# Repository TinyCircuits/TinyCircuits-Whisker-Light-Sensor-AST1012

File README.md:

# TinyCircuits Wireling Light Sensor
# AST1012 Rev2

The design files are located under design_files/ for the TinyCircuits AST1012 Rev 2 PCB. This is a Wireling board which features the AMS TSL2572 ambient light sensor with built in UV rejection filter and is also capable of operating in IR light environments. Its high sensitivity range enables it to operate even behind dark glass (such as in portable applications like Smartphones).

Format is in Cadsoft Eagle format - Eagle version 6.2 was used for the original design.

For more infomation on this, check out the product page at TinyCircuits.com

# License:

Design by TinyCircuits.
All design files are released under the Creative Commons Attribution Share-Alike 3.0 License, see the following link for details: http://creativecommons.org/licenses/by-sa/3.0

All text above must be included in any redistribution or derived design

This project uses designs and concepts developed as part of the Arduino project and the LilyPad project.  The TinyCircuits design files themselves (schematics, PCB and libraries) are not directly derived from these works' design files and have been created new, however the concepts and basic architecture behind the TinyDuino and TinyLily products are derived and we thank the hard work of the organizations below for their contributions to open-source hardware:
  
Original Arduino Uno Design by Team Arduino

LilyPad Arduino Design by Leah Buechley and Sparkfun Electronics

Please support the open-source hardware community

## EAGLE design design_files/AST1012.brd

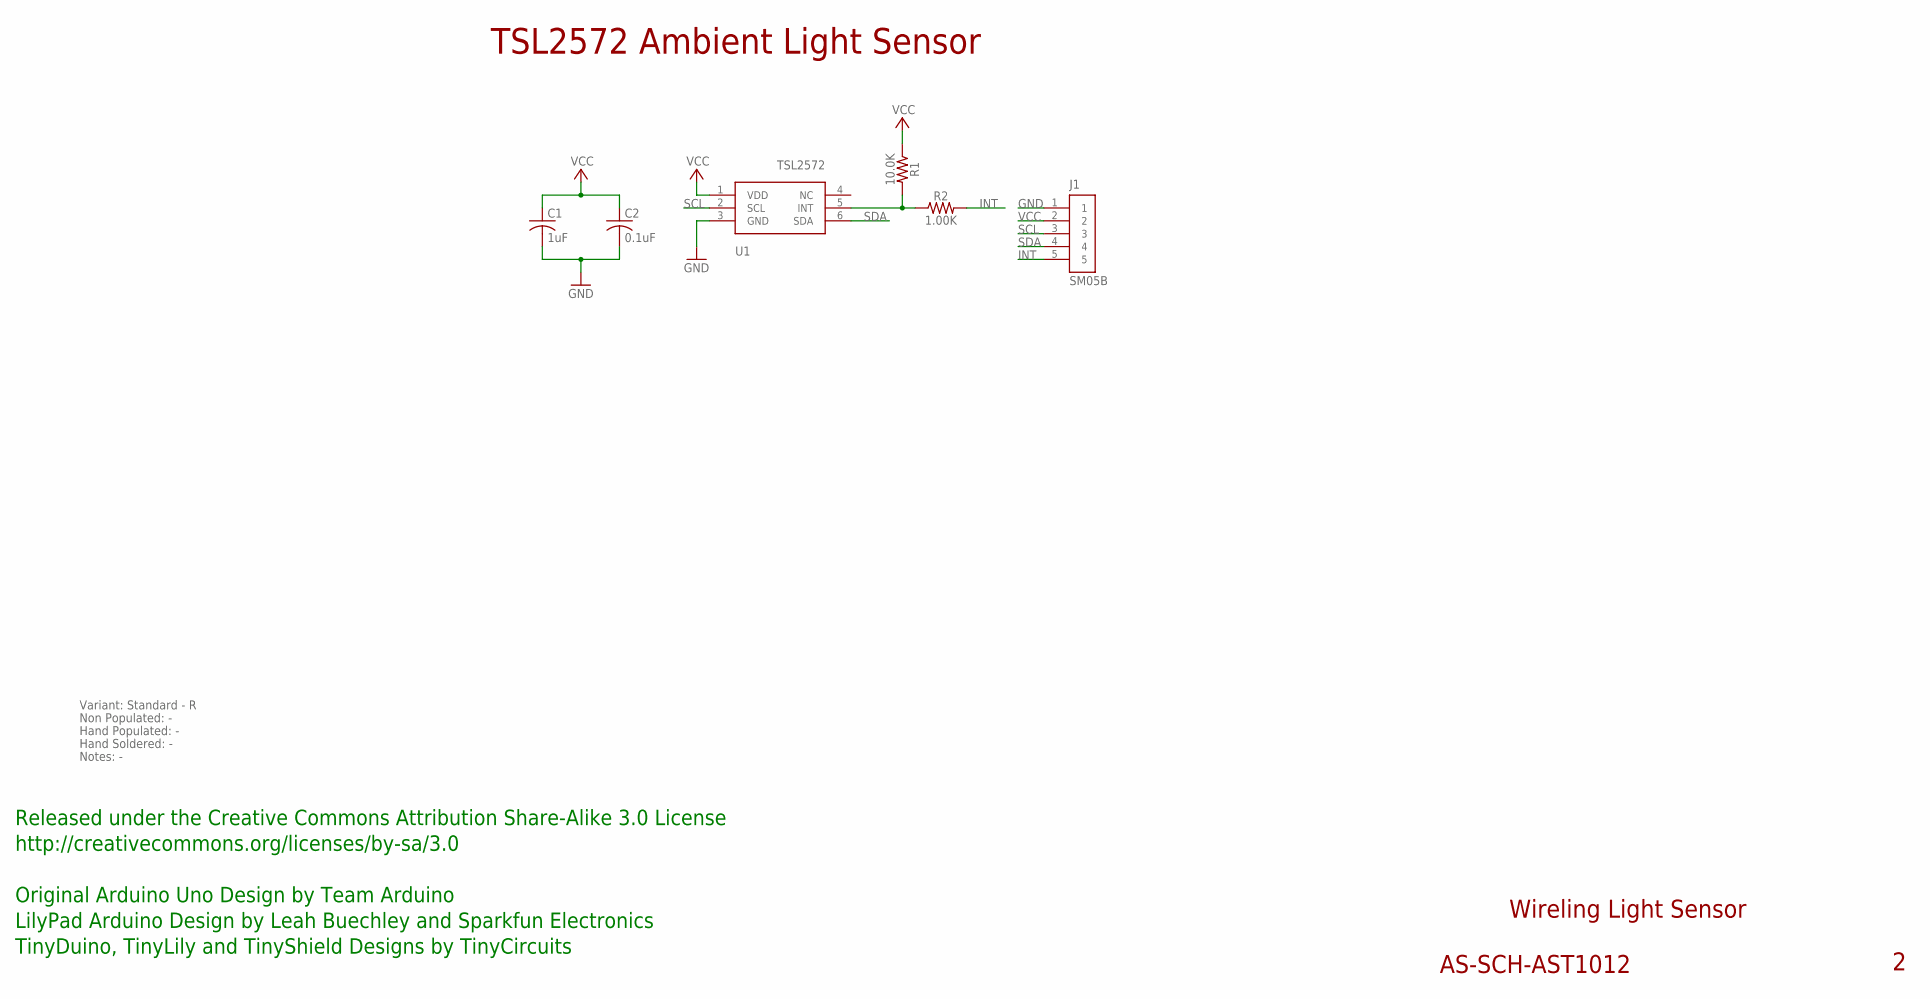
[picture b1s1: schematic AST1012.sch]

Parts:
C1: 1uF; C0603; PARTNO AS-ITM-00410
C2: 0.1uF; C0402
J1: SM05B; JST_SH_5X1_EDGE
R1: 10.0K; 0402; PARTNO AS-ITM-00032
R2: 1.00K; 0402; PARTNO AS-ITM-00003
U1: TSL2572; PARTNO AS-ITM-00116

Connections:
GND: C1.2, C2.2, J1.1, U1.3 (GND)
GPIO1: R1.2, R2.1, U1.5 (INT)
INT: J1.5, R2.2
SCL: J1.3, U1.2 (SCL)
SDA: J1.4, U1.6 (SDA)
VCC: C1.1, C2.1, J1.2, R1.1, U1.1 (VDD)

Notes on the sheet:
Wireling Light Sensor
AS-SCH-AST1012
TSL2572 Ambient Light Sensor
Released under the Creative Commons Attribution Share-Alike 3.0 License
http://creativecommons.org/licenses/by-sa/3.0
Original Arduino Uno Design by Team Arduino
TinyDuino, TinyLily and TinyShield Designs by TinyCircuits
LilyPad Arduino Design by Leah Buechley and Sparkfun Electronics
Variant: Standard - R
Non Populated: -
Hand Populated: -
Hand Soldered: -
Notes: -

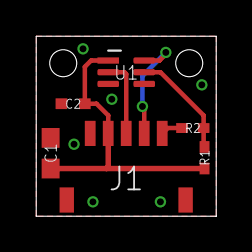
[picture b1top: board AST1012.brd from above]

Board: 2 copper layers, 10.0 x 10.0 mm, 7 parts (0 on the bottom side), 6 nets.

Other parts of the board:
U$1: DOCFIELD-TINYCIRCUITS-PCB

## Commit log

2019-08-02 added datasheet
2019-09-26 images and code fix
2019-10-28 name change
2019-11-22 power pin
2019-12-03 images
2019-12-04 code
2020-02-04 mass image update
2020-08-14 Add CAD data
2021-04-21 fix gain error
